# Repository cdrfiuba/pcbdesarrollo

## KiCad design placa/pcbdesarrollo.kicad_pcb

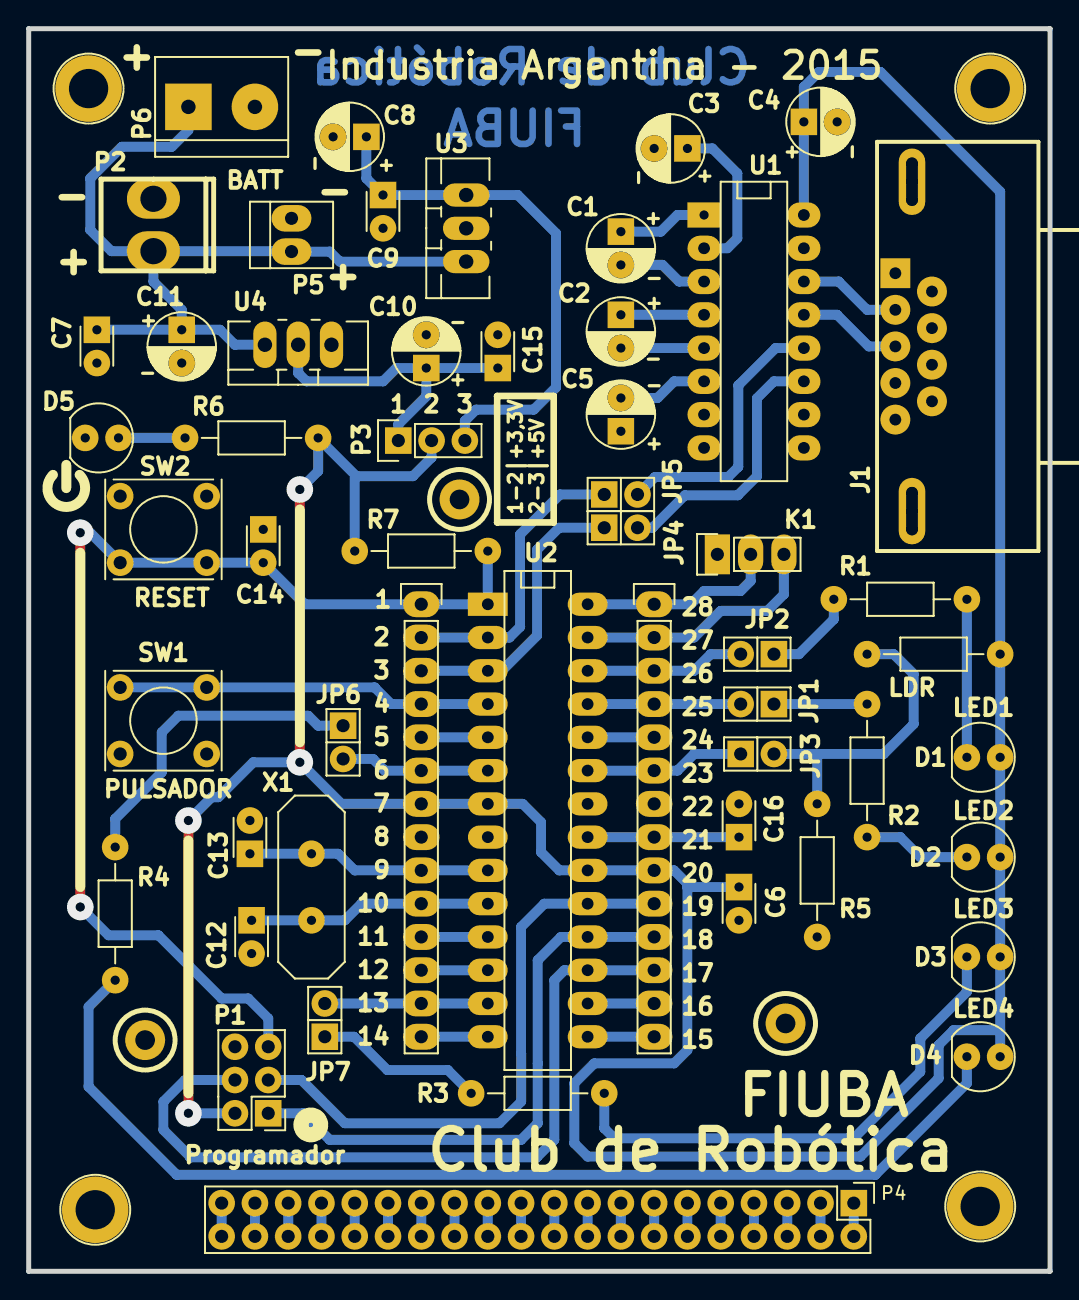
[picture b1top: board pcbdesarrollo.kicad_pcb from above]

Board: 2 copper layers, 78.0 x 94.9 mm, 60 parts (0 on the bottom side), 69 nets.

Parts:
1PIN, 1PIN#2, 1PIN#3, 1PIN#4, 1PIN#5, 1PIN#6, 1PIN#7: P***; 1pin
C1, C2, C3, C4, C5: 1uF; C_Radial_D5_L6_P2.5
C6, C7, C9, C14, C15, C16: 100nF; C_Disc_D3_P2.5
C8, C10, C11: 10uF; C_Radial_D5_L6_P2.5
C12, C13: 15p; C_Disc_D3_P2.5
CONN1, CONN2: CONN_14; Socket_Strip_Straight_1x14
D1: LED1; LED-3MM
D2: LED2; LED-3MM
D3: LED3; LED-3MM
D4: LED4; LED-3MM
D5: ON; LED-3MM
J1: DB9; DB9-F
JP1, JP2, JP3, JP4, JP5, JP6, JP7: JUMPER; Socket_Strip_Straight_1x02
K1: I2C; Socket_Strip_Straight_1x03
LDR: LDR 5-10 k; Resistor_Horizontal_RM10mm
P1: CONN_3X2; Socket_Strip_Straight_2x03
P2: BATT; molex_2_recto
P3: CONN_3; Socket_Strip_Straight_1x03
P4: CONN_02X20; Socket_Strip_Straight_2x20
P5: BATT; PINHEAD1-2
P6: BATT; bornier2
R1, R2, R3, R4, R6: 220; Resistor_Horizontal_RM10mm
R5: 1K; Resistor_Horizontal_RM10mm
R7: 10k; Resistor_Horizontal_RM10mm
SW1: PULSADOR; SW_PUSH_SMALL
SW2: RESET; SW_PUSH_SMALL
U1: MAX232; DIP-16__300_ELL
U2: AVR_ATMEGA88; DIP-28__300_ELL
U3: 7805FIX; TO-220_Neutral123_Vertical_LargePads
U4: AP1117T33; TO-220_Neutral123_Vertical_LargePads
X1: 18.432 Mhz; HC-18UV

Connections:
+3V3: C10.1, C15.1, P3.1, U4.2
+5V: C8.1, C9.1, P3.3, U3.3
/AREF: C16.1, CONN2.8, U2.21
/AT_5: CONN1.5, U2.5
/AT_9: C13.1, CONN1.9, U2.9, X1.2
/AT_10: C12.1, CONN1.10, U2.10, X1.1
/AT_11: CONN1.11, U2.11
/AT_12: CONN1.12, U2.12
/AT_14: CONN1.14, U2.14
/AT_15: CONN2.14, U2.15
/AT_16: CONN2.13, U2.16
/AT_24: CONN2.5, U2.24
/BOTON: CONN1.4, SW1.2, U2.4
/CC01: P4.1, P4.2
/CC02: P4.3, P4.4
/CC03: P4.5, P4.6
/CC04: P4.7, P4.8
/CC05: P4.9, P4.10
/CC06: P4.11, P4.12
/CC07: P4.13, P4.14
/CC08: P4.15, P4.16
/CC09: P4.17, P4.18
/CC10: P4.19, P4.20
/CC11: P4.21, P4.22
/CC12: P4.23, P4.24
/CC13: P4.25, P4.26
/CC14: P4.27, P4.28
/CC15: P4.29, P4.30
/CC16: P4.31, P4.32
/CC17: P4.33, P4.34
/CC18: P4.35, P4.36
/CC19: P4.37, P4.38
/CC20: P4.39, P4.40
/CONN_RX: J1.2, U1.14
/CONN_TX: J1.3, U1.13
/LDR: CONN2.6, JP3.1, U2.23
/LED1: CONN2.3, JP2.2, U2.26
/LED2: CONN2.4, JP1.2, U2.25
/LED3: CONN1.13, JP7.2, U2.13
/LED4: CONN1.6, JP6.2, U2.6
/MISO: CONN2.11, P1.1, U2.18
/MOSI: CONN2.12, P1.4, U2.17
/RESET: C14.2, CONN1.1, P1.5, R7.1, SW2.2, U2.1
/RXD: CONN1.2, JP5.1, U2.2
/SCK: CONN2.10, P1.3, U2.19
/SCL: CONN2.1, K1.2, U2.28
/SDA: CONN2.2, K1.3, U2.27
/TXD: CONN1.3, JP4.1, U2.3
GND: 1PIN.1, 1PIN#2.1, 1PIN#3.1, 1PIN#4.1, 1PIN#5.1, 1PIN#6.1, 1PIN#7.1, C3.2, C4.2, C5.1, C6.2, C7.2, C8.2, C9.2, C10.2, C11.2, C12.2, C13.2, C14.1, C15.2, C16.2, CONN1.8, CONN2.7, D5.2, J1.5, K1.1, P1.6, P2.2, P5.2, P6.2, R5.1, SW1.1, SW2.1, U1.8, U1.10, U1.15, U2.8, U2.22, U3.2, U4.1
unnamed: C1.1, U1.1
unnamed: C1.2, U1.3
unnamed: C2.1, U1.4
unnamed: C2.2, U1.5
unnamed: C3.1, U1.2
unnamed: C5.2, U1.6
unnamed: D1.2, R1.2
unnamed: D2.2, R2.2
unnamed: D3.2, R3.1
unnamed: D4.2, R4.2
unnamed: D5.1, R6.1
unnamed: JP1.1, R2.1
unnamed: JP2.1, R1.1
unnamed: JP3.2, LDR.2, R5.2
unnamed: JP4.2, U1.11
unnamed: JP5.2, U1.12
unnamed: JP6.1, R4.1
unnamed: JP7.1, R3.2
VCC: C4.1, C6.1, CONN1.7, CONN2.9, D1.1, D2.1, D3.1, D4.1, LDR.1, P1.2, P3.2, R6.2, R7.2, U1.16, U2.7, U2.20
VDD: C7.1, C11.1, P2.1, P5.1, P6.1, U3.1, U4.3

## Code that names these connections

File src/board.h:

#ifndef _BOARD_H_
#define _BOARD_H_

#include <avr/io.h>
#include <avr/interrupt.h>
#include <util/delay.h>
#include "defs.h"

/* Definiciones de Pines */

/*
    LED1
    PORT C.3
*/
#define PORT_LED1_NAME      C
#define LED1_NUMBER         3

#define PORT_LED1       def_port_reg(PORT_LED1_NAME)
#define PIN_LED1        def_pin_reg(PORT_LED1_NAME)
#define DDR_LED1        def_ddr_reg(PORT_LED1_NAME)

/*
    LED2
    PORT C.2
*/
#define PORT_LED2_NAME      C
#define LED2_NUMBER         2

#define PORT_LED2       def_port_reg(PORT_LED2_NAME)
#define PIN_LED2        def_pin_reg(PORT_LED2_NAME)
#define DDR_LED2        def_ddr_reg(PORT_LED2_NAME)

/*
    LED3
    PORT D.7
*/
#define PORT_LED3_NAME      D
#define LED3_NUMBER         7

#define PORT_LED3       def_port_reg(PORT_LED3_NAME)
#define PIN_LED3        def_pin_reg(PORT_LED3_NAME)
#define DDR_LED3        def_ddr_reg(PORT_LED3_NAME)

/*
    LED4
    PORT D.4
*/
#define PORT_LED4_NAME      D
#define LED4_NUMBER         4

#define PORT_LED4       def_port_reg(PORT_LED4_NAME)
#define PIN_LED4        def_pin_reg(PORT_LED4_NAME)
#define DDR_LED4        def_ddr_reg(PORT_LED4_NAME)

/*
    INTERRUPCION 0 (BOTON DE USUARIO)
    PORT D.0

*/
#define PORT_USER_BUTTON_NAME      D
#define USER_BUTTON_NUMBER         0

#define PORT_USER_BUTTON       def_port_reg(PORT_USER_BUTTON_NAME)
#define PIN_USER_BUTTON        def_pin_reg(PORT_USER_BUTTON_NAME)
#define DDR_USER_BUTTON        def_ddr_reg(PORT_USER_BUTTON_NAME)


/*
    LDR
    PORT C.0

*/
#define PORT_LDR_NAME      C
#define LDR_NUMBER         0

#define PORT_LDR       def_port_reg(PORT_LDR_NAME)
#define PIN_LDR        def_pin_reg(PORT_LDR_NAME)
#define DDR_LDR        def_ddr_reg(PORT_LDR_NAME)


/* Definiciones de Funciones */

// LED1
#define Led1Init()      SetBit(DDR_LED1, LED1_NUMBER)
#define Led1On()        ClearBit(PORT_LED1, LED1_NUMBER)
#define Led1Off()       SetBit(PORT_LED1, LED1_NUMBER)
#define IsLed1On()      IsBitClear(PORT_LED1, LED1_NUMBER)
#define Led1Toggle()    {if ( IsLed1On() ) Led1Off(); else Led1On();}

// LED2
#define Led2Init()      SetBit(DDR_LED2, LED2_NUMBER)
#define Led2On()        ClearBit(PORT_LED2, LED2_NUMBER)
#define Led2Off()       SetBit(PORT_LED2, LED2_NUMBER)
#define IsLed2On()      IsBitClear(PORT_LED2, LED2_NUMBER)
#define Led2Toggle()    {if ( IsLed2On() ) Led2Off(); else Led2On();}

// LED3
#define Led3Init()      SetBit(DDR_LED3, LED3_NUMBER)
#define Led3On()        ClearBit(PORT_LED3, LED3_NUMBER)
#define Led3Off()       SetBit(PORT_LED3, LED3_NUMBER)
#define IsLed3On()      IsBitClear(PORT_LED3, LED3_NUMBER)
#define Led3Toggle()    {if ( IsLed3On() ) Led3Off(); else Led3On();}

// LED4
#define Led4Init()      SetBit(DDR_LED4, LED4_NUMBER)
#define Led4On()        ClearBit(PORT_LED4, LED4_NUMBER)
#define Led4Off()       SetBit(PORT_LED4, LED4_NUMBER)
#define IsLed4On()      IsBitClear(PORT_LED4, LED4_NUMBER)
#define Led4Toggle()    {if ( IsLed4On() ) Led4Off(); else Led4On();}

// BOTON
#define BotonPullUp()   SetBit(PORT_USER_BUTTON, USER_BUTTON_NUMBER)
#define BotonInit()     ClearBit(DDR_USER_BUTTON, USER_BUTTON_NUMBER)
#define IsBotonPush()   IsBitClear(PORT_USER_BUTTON, USER_BUTTON_NUMBER)

#endif

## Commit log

2011-05-19 Agrego el esquematico de la primera version.
2011-07-04 Muevo los archivos de kicad a un directorio espec?fico.
2011-07-04 Agrego el firmware de prueba para la placa. Prende y apaga los leds y env?a un mensaje por puerto serie. TODO: utilizar el bot?n.
2011-07-04 Agrego el hgignore.
2011-11-29 Modificaciones a la placa para usarla para pruebas del estandar de interoperabilidad del club
2011-12-03 empece pcb pero esta feo todavia
2011-12-10 sigo haciendo modificaciones
2011-12-11 ya casi esta
2011-12-12 primera version de la placa terminada
2011-12-29 agrego archivo que faltaba
2011-12-29 merge
2012-02-28 M?s cambios a la placa.
2012-03-17 placa modificada
2012-03-17 subo avances de placa
2012-03-18 falta revision, se cambio el regulador de 3.3V al HT7133
2012-03-19 modificamos el esquematico para incluir el cristal y un pulsador de reset
2012-03-20 Placa casi lista, falta ver el conector de bateria y el conector para la LDR
2012-03-21 agregue conector bateria y serigrafia
2012-03-21 terminamos serigrafia y agregamos puntos de medicion
2012-03-21 agrego comnentario por agujeros ovalados
2012-04-05 Arreglo board.h para reflejar los leds de la nueva placa de desarrollo. Agrego un codigo de prueba.
2012-04-20 agrego las bibliotecas usadas en la placa
2012-04-20 Agregoel pin de interrupcion al Board.h como USER_BUTTON, y la macro de iniciaci?n
2012-04-20 Agrego la funci?n de chequeo del estado del boton
2012-04-20 Agrego MACRO de pullup del boton
2012-05-17 Agrego la biblioteca para comunicacion serie
2012-05-18 Cambios varios en el codigo de prueba
2012-05-26 modificaciones y comentarios al Makefile
2012-06-30 hago algunos ajustes a la biblioteca de serial y al ejemplo para probarlo, ahora esta funcionando con el cristal externo
2012-06-30 cierro el branch i2c
2012-06-30 detalle del Makefile
2012-06-30 hago un makefile mas rebuscado
2012-11-23 muevo todo a library
2013-02-10 actualizacion de la biblioteca, cambios en la forma de compilar distintos proyectos
2013-02-10 actualizo el ejemplo de serie a la nueva version de biblioteca y Makefile
2013-02-10 agrego el ejemplo mas basico, que no usa la biblioteca
2013-02-10 arreglo el ejemplo blinky y un error en defs.h
2013-02-10 agrego un ejemplo con el ADC y el LDR
2013-02-10 Agrego un ejemplo para usar un display de 16 caracteres de 2 lineas
2013-02-20 Corrijo un error en el sistema de compilacion, ahora se genera bien el hex
2013-02-20 Agrego una version muy simplificada del cubo de leds. sirve para testear todas las filas y columnas
2013-02-20 agrego el archivo de Makefile base, que sirve de plantilla para cada proyecto
2013-02-20 cambio la ubicacion de la fila 3 en el mapeo de pines
2013-04-19 puntito en movimiento
2013-07-06 arreglo un define en el clock
2013-07-27 agrego el archivo config.mk para configurar una unica vez la bilioteca y no tener que hacerlo en cada proyecto
2013-09-16 subo paleta para el LCI
2013-09-16 Corrijo el palet que subio Octavio con el nombre pcbdesarrollo-palet, y paso todos los archivos de fabricacion del palet a la carpeta Fabricacion. El palet tiene 4 agujeros por agujero ovalado del se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
2013-09-16 Agrego los 4 agujeros para el conector serie
2013-09-18 Arreglo el error sobre los archivos de fabricacion de que los agujeros no se centraban con el borde
2015-02-20 Version 2.0 de la placa de desarrollo. Se paso al nuevo kicad, se sac? la parte experimental y se agregaron jumpers para desconectar los perifericos agregados ala placa.
2015-03-05 version 2 del pcb
2015-04-29 actualizacion de la placa
2015-04-29 corrijo un capacitor del MAX232 que estaba conectado al reves
2015-04-29 corrijo un capacitor del MAX232 que estaba conectado al reves, incluyo el pcb
2015-04-29 arreglo la serigrafia y elimino archivos innecesarios
2016-01-08 agrego funcion putc
